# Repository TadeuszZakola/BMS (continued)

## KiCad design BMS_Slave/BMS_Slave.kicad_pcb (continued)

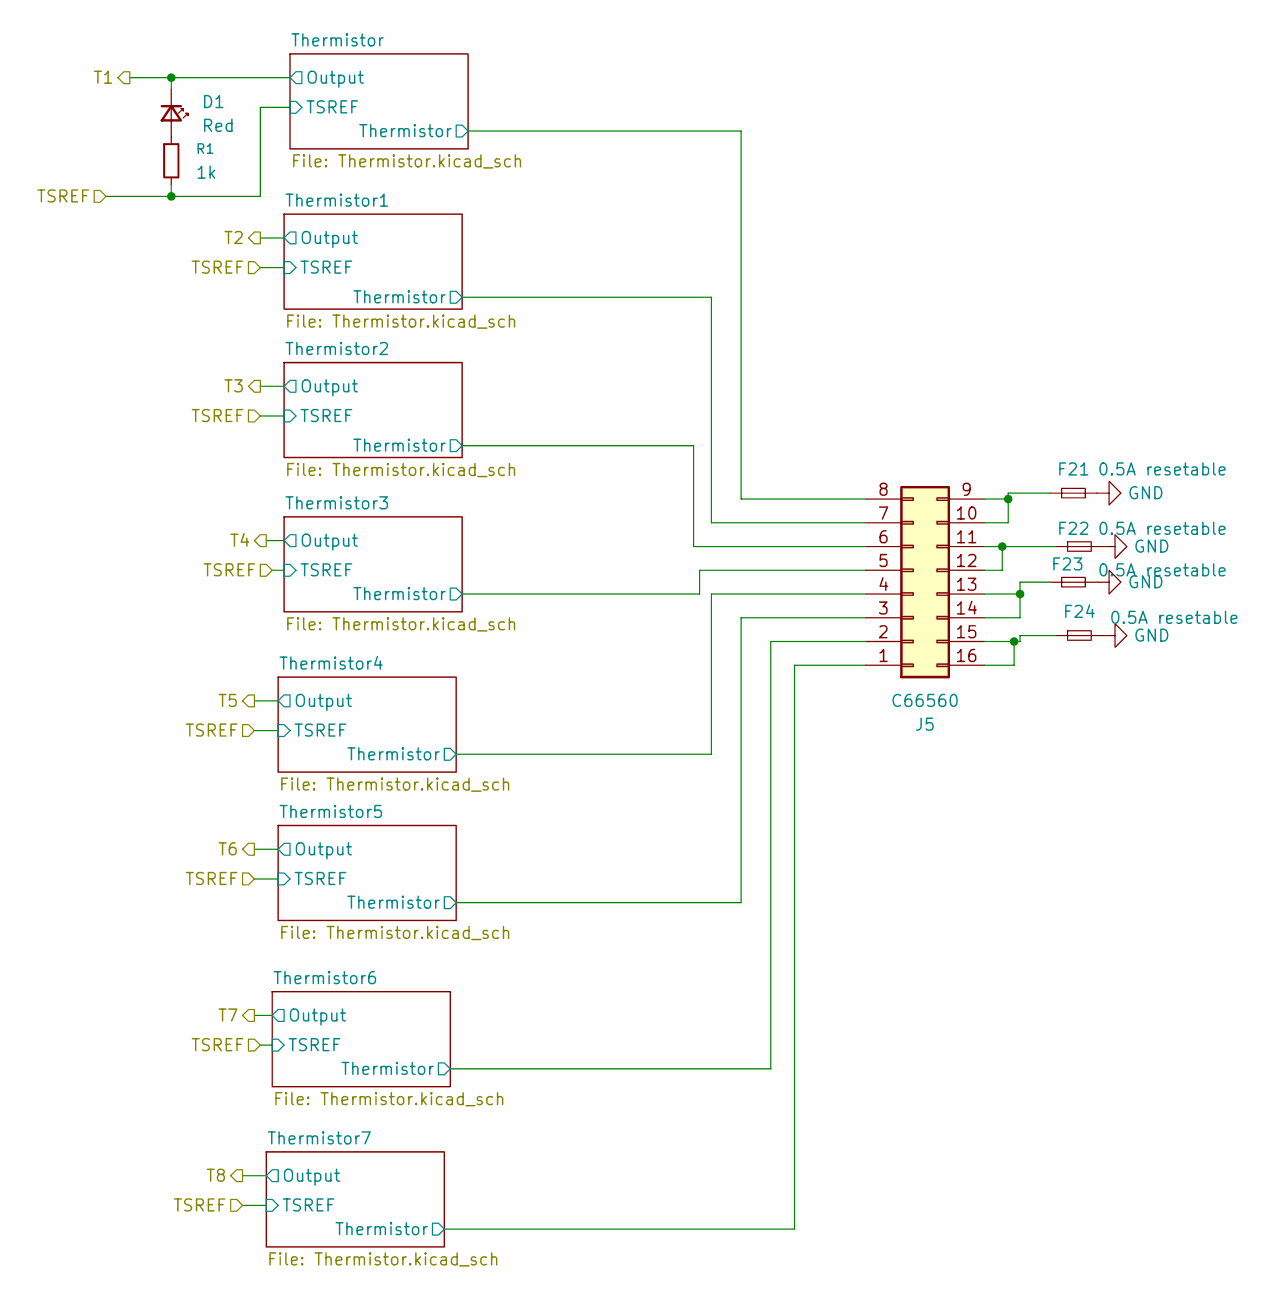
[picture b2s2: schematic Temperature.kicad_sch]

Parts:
D1: Red; LED_0603_1608Metric
F21, F22, F23, F24: 0.5A resetable; Fuse_0805_2012Metric
J5: C66560; JST_PHD_S16B-PHDSS_2x08_P2.00mm_Horizontal
R1: 1k; R_0603_1608Metric

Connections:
/Temperature/T1: D1.1 (K); also elsewhere on the board
/Temperature/TSREF: R1.2; also elsewhere on the board
/Temperature/Thermistor1/Thermistor: J5.7; also elsewhere on the board
/Temperature/Thermistor2/Thermistor: J5.6; also elsewhere on the board
/Temperature/Thermistor3/Thermistor: J5.5; also elsewhere on the board
/Temperature/Thermistor4/Thermistor: J5.4; also elsewhere on the board
/Temperature/Thermistor5/Thermistor: J5.3; also elsewhere on the board
/Temperature/Thermistor6/Thermistor: J5.2; also elsewhere on the board
/Temperature/Thermistor7/Thermistor: J5.1; also elsewhere on the board
/Temperature/Thermistor/Thermistor: J5.8; also elsewhere on the board
GND: F21.2, F22.2, F23.2, F24.2; also elsewhere on the board
unnamed: D1.2 (A), R1.1
unnamed: F21.1, J5.9, J5.10
unnamed: F22.1, J5.11, J5.12
unnamed: F23.1, J5.13, J5.14
unnamed: F24.1, J5.15, J5.16

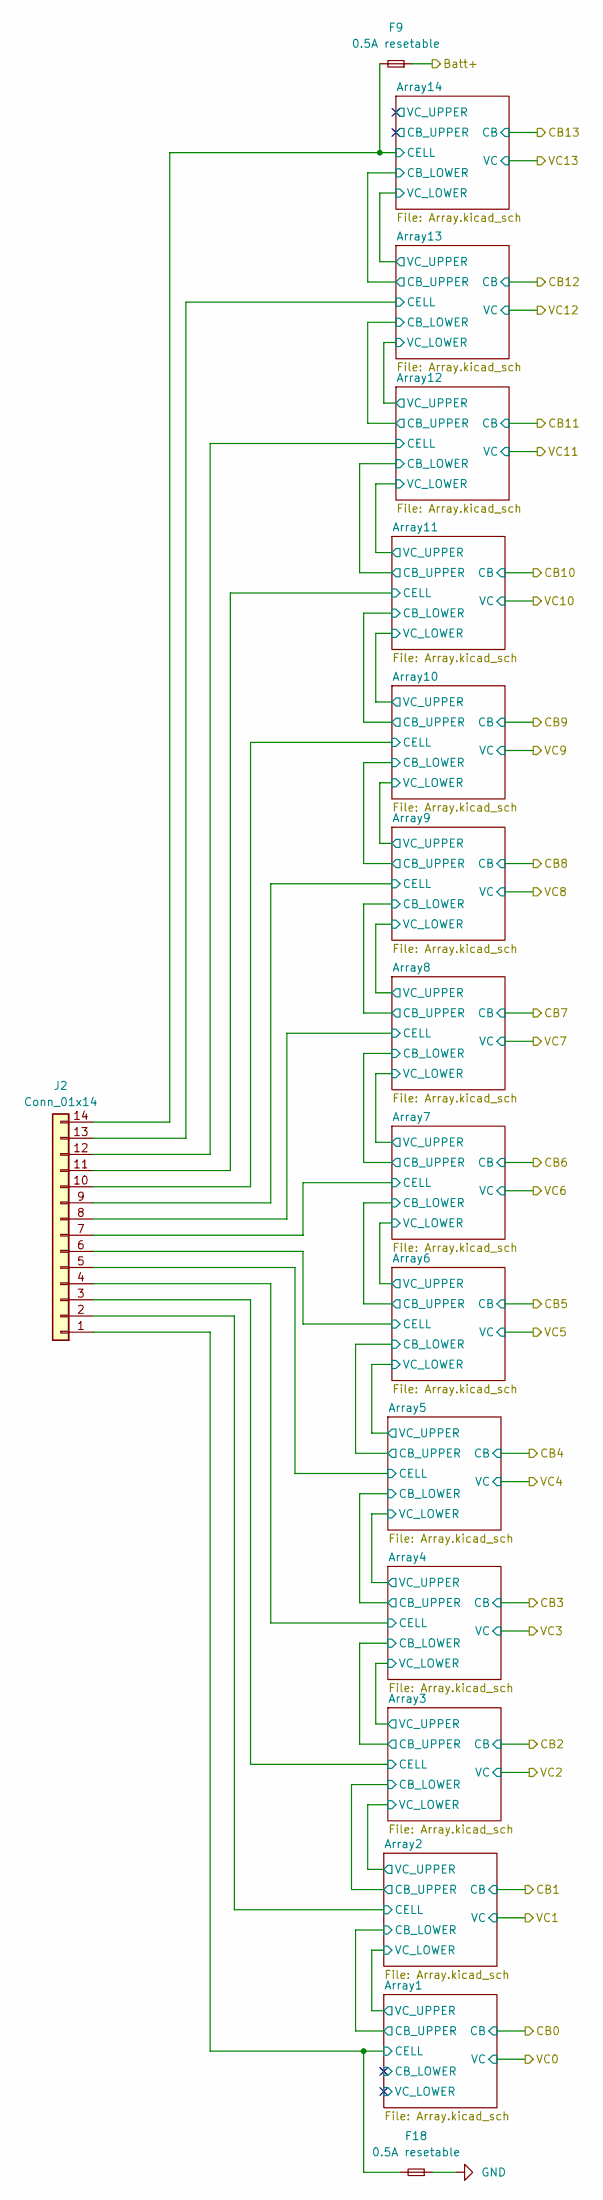
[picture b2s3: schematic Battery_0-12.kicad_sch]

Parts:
F9, F18: 0.5A resetable; Fuse_0805_2012Metric
J2: Conn_01x14; XY-XHB2.54-14A21

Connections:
/Battery/Array1/CELL: F18.2, J2.1; also elsewhere on the board
/Battery/Array2/CELL: J2.2; also elsewhere on the board
/Battery/Array3/CELL: J2.3; also elsewhere on the board
/Battery/Array4/CELL: J2.4; also elsewhere on the board
/Battery/Array5/CELL: J2.5; also elsewhere on the board
/Battery/Array6/CELL: J2.6; also elsewhere on the board
/Battery/Array7/CELL: J2.7; also elsewhere on the board
/Battery/Array8/CELL: J2.8; also elsewhere on the board
/Battery/Array9/CELL: J2.9; also elsewhere on the board
/Battery/Array10/CELL: J2.10; also elsewhere on the board
/Battery/Array11/CELL: J2.11; also elsewhere on the board
/Battery/Array12/CELL: J2.12; also elsewhere on the board
/Battery/Array13/CELL: J2.13; also elsewhere on the board
/Battery/Array14/CELL: F9.2, J2.14; also elsewhere on the board
/Battery/Batt+: F9.1; also elsewhere on the board
GND: F18.1; also elsewhere on the board

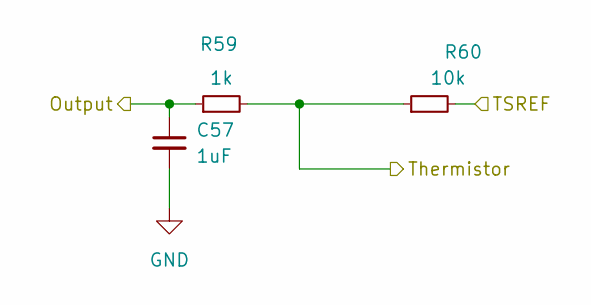
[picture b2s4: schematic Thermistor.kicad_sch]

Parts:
C57: 1uF; C_0603_1608Metric_Pad1.08x0.95mm_HandSolder
R59: 1k; R_0603_1608Metric_Pad0.98x0.95mm_HandSolder
R60: 10k; R_0603_1608Metric_Pad0.98x0.95mm_HandSolder

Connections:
/Temperature/T1: C57.1, R59.1; also elsewhere on the board
/Temperature/TSREF: R60.2; also elsewhere on the board
/Temperature/Thermistor/Thermistor: R59.2, R60.1; also elsewhere on the board
GND: C57.2; also elsewhere on the board

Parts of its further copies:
C58, C59, C60, C61, C62, C63, C64: 1uF; C_0603_1608Metric_Pad1.08x0.95mm_HandSolder
R61, R63, R65, R67, R69, R71, R73: 1k; R_0603_1608Metric_Pad0.98x0.95mm_HandSolder
R62, R64, R66, R68, R70, R72, R74: 10k; R_0603_1608Metric_Pad0.98x0.95mm_HandSolder

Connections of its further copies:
/Temperature/T2: C58.1, R61.1; also elsewhere on the board
/Temperature/T3: C59.1, R63.1; also elsewhere on the board
/Temperature/T4: C60.1, R65.1; also elsewhere on the board
/Temperature/T5: C61.1, R67.1; also elsewhere on the board
/Temperature/T6: C62.1, R69.1; also elsewhere on the board
/Temperature/T7: C63.1, R71.1; also elsewhere on the board
/Temperature/T8: C64.1, R73.1; also elsewhere on the board
/Temperature/TSREF: R62.2, R64.2, R66.2, R68.2, R70.2, R72.2, R74.2; also elsewhere on the board
/Temperature/Thermistor1/Thermistor: R61.2, R62.1; also elsewhere on the board
/Temperature/Thermistor2/Thermistor: R63.2, R64.1; also elsewhere on the board
/Temperature/Thermistor3/Thermistor: R65.2, R66.1; also elsewhere on the board
/Temperature/Thermistor4/Thermistor: R67.2, R68.1; also elsewhere on the board
/Temperature/Thermistor5/Thermistor: R69.2, R70.1; also elsewhere on the board
/Temperature/Thermistor6/Thermistor: R71.2, R72.1; also elsewhere on the board
/Temperature/Thermistor7/Thermistor: R73.2, R74.1; also elsewhere on the board
GND: C58.2, C59.2, C60.2, C61.2, C62.2, C63.2, C64.2; also elsewhere on the board

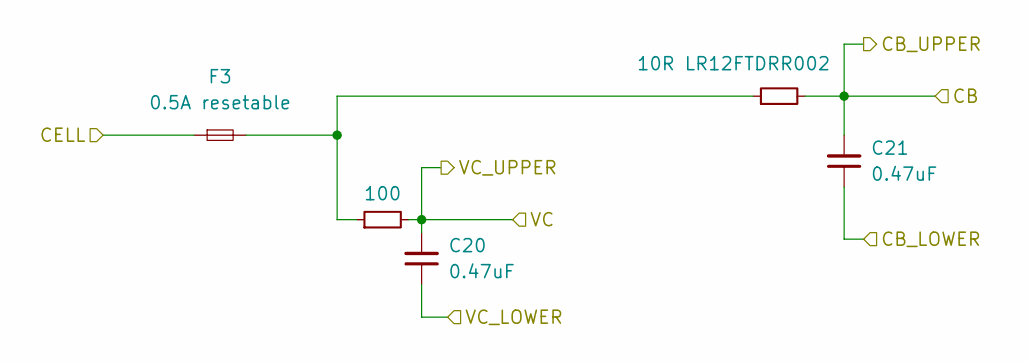
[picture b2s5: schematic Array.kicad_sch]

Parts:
C20, C21: 0.47uF; C_0603_1608Metric
F3: 0.5A resetable; Fuse_0805_2012Metric
R22: 100; R_0603_1608Metric
R35: 10R LR12FTDRR002; R_2512_6332Metric

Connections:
/Battery/Array1/CB_LOWER: C21.1
/Battery/Array1/CELL: F3.1; also elsewhere on the board
/Battery/Array1/VC_LOWER: C20.1
/CB0: C21.2, R35.2; also elsewhere on the board
/VC0: C20.2, R22.2; also elsewhere on the board
unnamed: F3.2, R22.1, R35.1

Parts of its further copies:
C22, C23, C24, C25, C26, C27, C28, C29, C30, C31, C32, C33, C34, C35, C36, C37, C38, C39, C40, C41, C42, C43, C44, C45, C46, C47: 0.47uF; C_0603_1608Metric
F4, F5, F6, F7, F8, F10, F11, F12, F13, F14, F15, F16, F17: 0.5A resetable; Fuse_0805_2012Metric
R23, R24, R25, R26, R27, R28, R29, R30, R31, R32, R33, R34, R48: 100; R_0603_1608Metric
R36, R37, R38, R39, R40, R41, R42, R43, R44, R45, R46, R47, R49: 10R LR12FTDRR002; R_2512_6332Metric

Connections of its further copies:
/Battery/Array2/CELL: F4.1; also elsewhere on the board
/Battery/Array3/CELL: F5.1; also elsewhere on the board
/Battery/Array4/CELL: F6.1; also elsewhere on the board
/Battery/Array5/CELL: F7.1; also elsewhere on the board
/Battery/Array6/CELL: F8.1; also elsewhere on the board
/Battery/Array7/CELL: F10.1; also elsewhere on the board
/Battery/Array8/CELL: F11.1; also elsewhere on the board
/Battery/Array9/CELL: F12.1; also elsewhere on the board
/Battery/Array10/CELL: F13.1; also elsewhere on the board
/Battery/Array11/CELL: F14.1; also elsewhere on the board
/Battery/Array12/CELL: F15.1; also elsewhere on the board
/Battery/Array13/CELL: F16.1; also elsewhere on the board
/Battery/Array14/CELL: F17.1; also elsewhere on the board
/CB0: C23.1; also elsewhere on the board
/CB1: C23.2, C25.1, R36.2; also elsewhere on the board
/CB2: C25.2, C27.1, R37.2; also elsewhere on the board
/CB3: C27.2, C29.1, R38.2; also elsewhere on the board
/CB4: C29.2, C31.1, R39.2; also elsewhere on the board
/CB5: C31.2, C33.1, R40.2; also elsewhere on the board
/CB6: C33.2, C35.1, R41.2; also elsewhere on the board
/CB7: C35.2, C37.1, R42.2; also elsewhere on the board
/CB8: C37.2, C39.1, R43.2; also elsewhere on the board
/CB9: C39.2, C41.1, R44.2; also elsewhere on the board
/CB10: C41.2, C43.1, R45.2; also elsewhere on the board
/CB11: C43.2, C45.1, R46.2; also elsewhere on the board
/CB12: C45.2, C47.1, R47.2; also elsewhere on the board
/CB13: C47.2, R49.2; also elsewhere on the board
/VC0: C22.1; also elsewhere on the board
/VC1: C22.2, C24.1, R23.2; also elsewhere on the board
/VC2: C24.2, C26.1, R24.2; also elsewhere on the board
/VC3: C26.2, C28.1, R25.2; also elsewhere on the board
/VC4: C28.2, C30.1, R26.2; also elsewhere on the board
/VC5: C30.2, C32.1, R27.2; also elsewhere on the board
/VC6: C32.2, C34.1, R28.2; also elsewhere on the board
/VC7: C34.2, C36.1, R29.2; also elsewhere on the board
/VC8: C36.2, C38.1, R30.2; also elsewhere on the board
/VC9: C38.2, C40.1, R31.2; also elsewhere on the board
/VC10: C40.2, C42.1, R32.2; also elsewhere on the board
/VC11: C42.2, C44.1, R33.2; also elsewhere on the board
/VC12: C44.2, C46.1, R34.2; also elsewhere on the board
/VC13: C46.2, R48.2; also elsewhere on the board
unnamed: F4.2, R23.1, R36.1
unnamed: F5.2, R24.1, R37.1
unnamed: F6.2, R25.1, R38.1
unnamed: F7.2, R26.1, R39.1
unnamed: F8.2, R27.1, R40.1
unnamed: F10.2, R28.1, R41.1
unnamed: F11.2, R29.1, R42.1
unnamed: F12.2, R30.1, R43.1
unnamed: F13.2, R31.1, R44.1
unnamed: F14.2, R32.1, R45.1
unnamed: F15.2, R33.1, R46.1
unnamed: F16.2, R34.1, R47.1
unnamed: F17.2, R48.1, R49.1

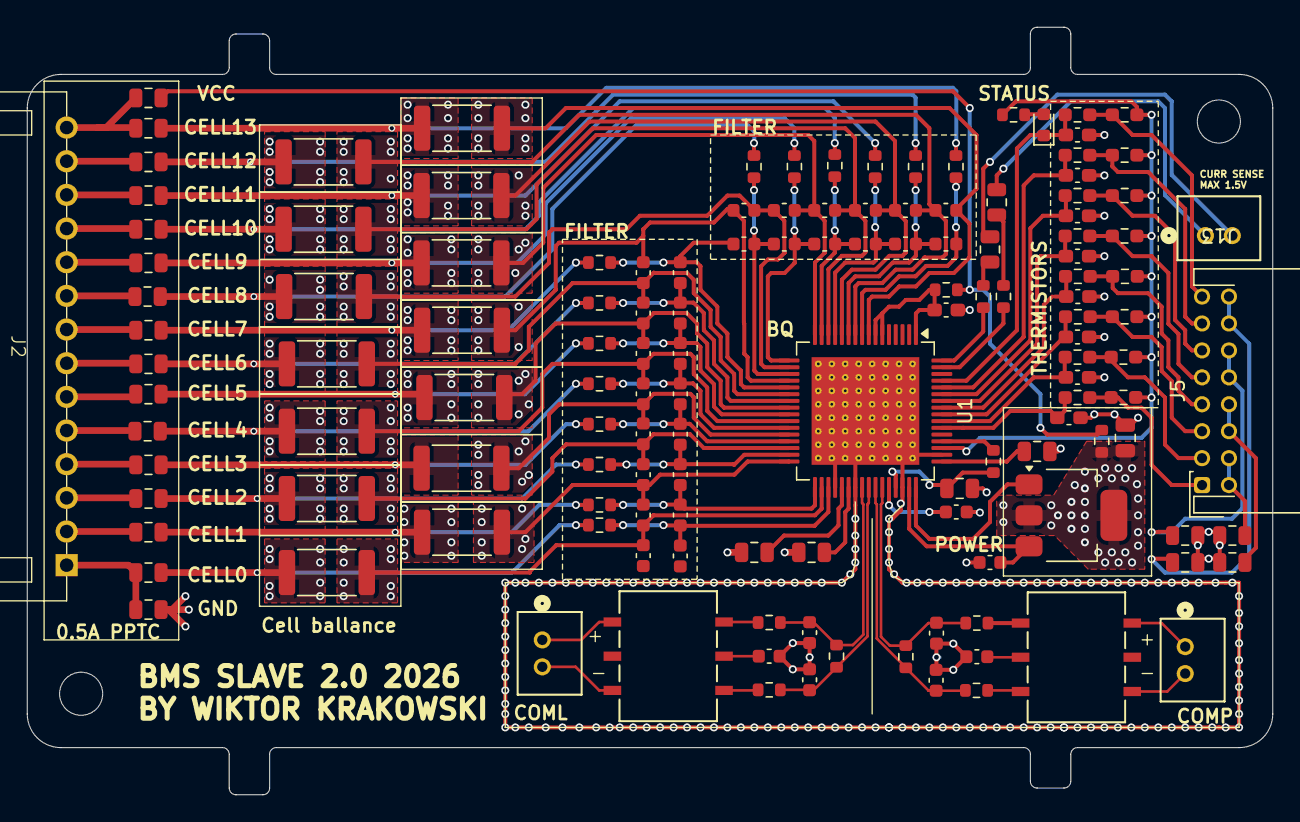
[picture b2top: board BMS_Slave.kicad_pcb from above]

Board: 4 copper layers, 92.5 x 57.0 mm, 140 parts (0 on the bottom side), 110 nets.

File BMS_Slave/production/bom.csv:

Designator,Footprint,Quantity,Value,LCSC Part #
C2,0805,1,0.22uF,
"C20, C21, C22, C23, C24, C25, C26, C27, C28, C29, C30, C31, C32, C33, C34, C35, C36, C37, C38, C39, C40, C41, C42, C43, C44, C45, C46, C47",0603,28,0.47uF,
"C3, C9",0603,2,0.1uF,
C4,0603,1,10nF,
"C48, C49, C50, C51, C52, C53",0603,6,220pF,
"C5, C8",0805,2,1uF,
"C57, C58, C59, C60, C61, C62, C63, C64",0603,8,1uF,
C6,0805,1,4.7uF,
C7,0805,1,2.2uF,
"F10, F11, F12, F13, F14, F15, F16, F17, F18, F3, F4, F5, F6, F7, F8, F9",0805,16,0.5A resetable,
"J1, J16, J17, J18, J19, J20, J21, J22, J23, J24, J25, J26, J27, J28, J29, J30",SolderWirePad_1x01_SMD_2x4mm,16,Conn_01x01_Socket,
J10,SolderWirePad_1x01_SMD_5x10mm,1,Batt 7,
J11,SolderWirePad_1x01_SMD_5x10mm,1,Batt 6,
J12,SolderWirePad_1x01_SMD_5x10mm,1,Batt 2,
J13,SolderWirePad_1x01_SMD_5x10mm,1,Batt 5,
J14,SolderWirePad_1x01_SMD_5x10mm,1,Batt 1,
J15,SolderWirePad_1x01_SMD_5x10mm,1,Batt 0,
J2,SolderWirePad_1x01_SMD_5x10mm,1,Batt 13,
J3,SolderWirePad_1x01_SMD_5x10mm,1,Batt 12,
"J33, J34",DSUB-9_Pins_Vertical_P2.77x2.84mm_MountingHoles,2,Dsub 9,
J4,SolderWirePad_1x01_SMD_5x10mm,1,Batt 11,
J5,SolderWirePad_1x01_SMD_5x10mm,1,Batt 10,
J6,SolderWirePad_1x01_SMD_5x10mm,1,Batt 9,
J7,SolderWirePad_1x01_SMD_5x10mm,1,Batt 8,
J8,SolderWirePad_1x01_SMD_5x10mm,1,Batt 4,
J9,SolderWirePad_1x01_SMD_5x10mm,1,Batt 3,
Q8,SOT-223-3_TabPin2,1,FZT653TA,
R2,0603,1,300,
"R22, R23, R24, R25, R26, R27, R28, R29, R30, R31, R32, R33, R34, R48",0603,14,100,
"R35, R36, R37, R38, R39, R40, R41, R42, R43, R44, R45, R46, R47, R49",2512,14,10R LR12FTDRR002,
R4,0603,1,30,
R5,0603,1,0R,
"R58, R59, R61, R63, R65, R67, R69, R71, R73, R77",0603,10,1k,
"R60, R62, R64, R66, R68, R70, R72, R74",0603,8,10k,
"R75, R76, R78, R79",0603,4,49,
"T2, T3",IC6_SM91502ALA-E_BRN,2,TM0608SR,
U1,Texas_TQFP-64-1EP_10x10mm_P0.5mm_EP8x8mm_Mask4.44x4.44mm_ThermalVias,1,BQ79614PAPRQ1,

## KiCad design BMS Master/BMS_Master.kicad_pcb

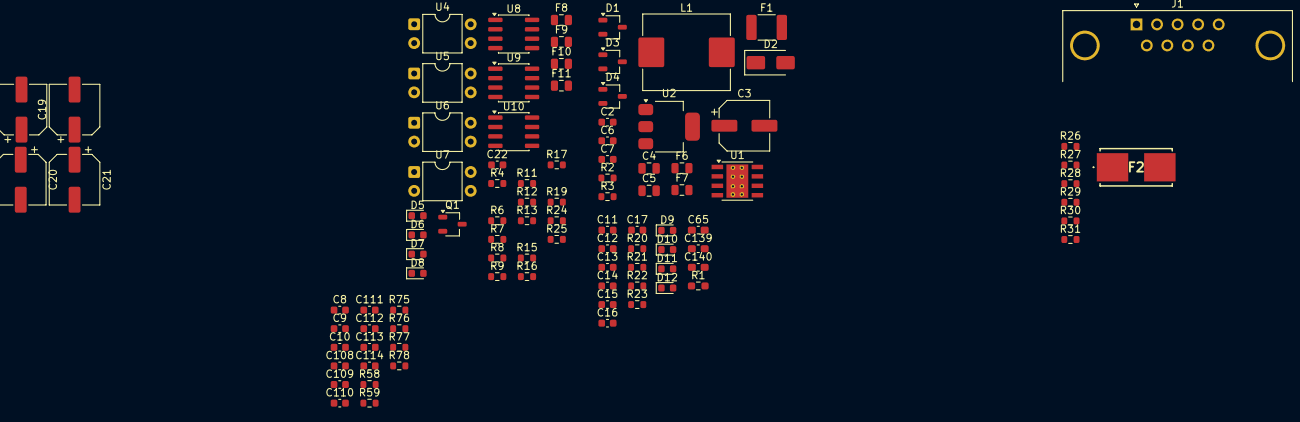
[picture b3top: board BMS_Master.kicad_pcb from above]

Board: 2 copper layers, 96 parts (0 on the bottom side), 48 nets, no tracks yet.

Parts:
C2, C6, C7, C8, C9, C10, C11, C12, C13, C14, C15, C16, C17, C22: CC0603KRX7R9BB104; C_0603_1608Metric
C3, C18, C19, C20, C21: MS221M160E5R8R4Z00ZZ; CP_Elec_6.3x5.8
C4, C5: CL21B224KBFNNNE; C_0805_2012Metric
C65: 1uF; C_0603_1608Metric_Pad1.08x0.95mm_HandSolder
C108, C109, C110, C111, C112, C113, C114: CL10B224KA8NNNC; C_0603_1608Metric
C139, C140: 2.2n; C_0603_1608Metric_Pad1.08x0.95mm_HandSolder
D1, D3, D4: PSM712-LF-T7; TSOT-23
D2: B340A; D_SMA
D5, D6, D7, D8, D9, D10, D11, D12: KT-0603R; LED_0603_1608Metric
F1: SMD1812P200TF16; C_1812_4532Metric
F2: 01550900M
F6, F7, F8, F9, F10, F11: 0.5A resetable; Fuse_0805_2012Metric
J1: DE9_Pins; DSUB-9_Pins_Horizontal_P2.77x2.84mm_EdgePinOffset4.94mm_Hou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
L1: CYA1040-15UH; L_Chilisin_BMRF00101040
Q1: AO3401A; TSOT-23
R1: 100k; R_0603_1608Metric_Pad0.98x0.95mm_HandSolder
R2: 0603WAF1002T5E; R_0603_1608Metric
R3: 0603WAF3301T5E; R_0603_1608Metric
R4, R11, R15, R19: 0603WAF2200T5E; R_0603_1608Metric
R6, R7, R13, R17: 0603WAF4991T5E; R_0603_1608Metric
R8, R9, R12, R16, R20, R21, R22, R23, R25, R30, R31: 0603WAF1000T5E; R_0603_1608Metric
R24, R26, R27, R28, R29, R58: 0603WAF1001T5E; R_0603_1608Metric
R59: 1k; R_0603_1608Metric
R75, R76, R77, R78: 0603WAF499JT5E; R_0603_1608Metric
U1: TPS5430DDA; TI_SO-PowerPAD-8_ThermalVias
U2: AMS1117-3.3; SOT-223-3_TabPin2
U4, U5, U6, U7: LTV-817; DIP-4_W7.62mm
U8: ACS711ELCTR-12AB-T; SOIC-8_3.9x4.9mm_P1.27mm
U9, U10: ACS711xLCTR-12AB; SOIC-8_3.9x4.9mm_P1.27mm

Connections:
/BQ Interface/5V: C10.1, C108.1
/BQ Interface/COMHN: C111.1, R58.1, R76.1
/BQ Interface/COMHP: C110.1, R58.2, R75.1
/BQ Interface/COMLN: C113.1, R59.1, R78.1
/BQ Interface/COMLP: C112.1, R59.2, R77.1
/Power/3.3V: C6.1, C7.1, D4.1 (A1), D4.2 (A2), F7.2
/Power/5V: C5.1, D3.1 (A1), D3.2 (A2), F1.2, U2.3 (VI)
/STM/3.3V: C11.1, C12.2, C13.2, C14.1, C15.1, C16.1, C17.1, C65.2, R20.1, R21.1, R22.1, R23.1
/STM_IO/3.3V: C22.1, R6.1, R7.1, R13.1, R17.1, R26.2, R27.2, R28.2, R29.2, U8.8 (VCC)
/STM_IO/Power_output_1: J1.5 (5_5), U8.3 (IP-), U8.4 (IP-)
GND: C3.2, C4.2, C5.2, C6.2, C7.2, C8.2, C9.1, C10.2, C11.2, C12.1, C13.1, C14.2, C15.2, C16.2, C17.2, C65.1, C108.2, C109.2, C110.2, C111.2, C112.2, C113.2, C114.2, C139.1, D1.3 (common), D2.2 (A), D3.3 (common), D4.3 (common), R1.1, R3.2, U1.6 (GND), U1.9 (GNDPAD), U2.1 (GND)
unnamed: C3.1, F1.1, L1.2, R2.1
unnamed: C18.2, C19.2, C20.2, C21.2
unnamed: D1.1 (A1), D1.2 (A2), F6.2, U1.7 (VIN)
unnamed: C2.2, D2.1 (K), L1.1, U1.8 (PH)
unnamed: D5.2 (A), R29.1
unnamed: D5.1 (K), R6.2, R8.2, U4.4
unnamed: D6.2 (A), R7.2, R9.2, U5.4
unnamed: D6.1 (K), R28.1
unnamed: D7.2 (A), R12.2, R13.2, U6.4
unnamed: D7.1 (K), R27.1
unnamed: D8.2 (A), R16.2, R17.2, U7.4
unnamed: D8.1 (K), R26.1
unnamed: D9.2 (A), R20.2
unnamed: D10.2 (A), R21.2
unnamed: D11.2 (A), R22.2
unnamed: D12.2 (A), R23.2
unnamed: F2.2, U8.1 (IP+), U8.2 (IP+)
unnamed: F8.1, R4.1
unnamed: F9.1, R11.1
unnamed: F10.1, R15.1
unnamed: F11.1, R19.1
unnamed: C18.1, C19.1, C20.1, C21.1, Q1.3 (D), R24.1
unnamed: Q1.1 (G), R24.2, R25.2
unnamed: F2.1, Q1.2 (S)
unnamed: R4.2, U4.1
unnamed: R11.2, U5.1
unnamed: R15.2, U6.1
unnamed: R19.2, U7.1
unnamed: C2.1, U1.1 (BOOT)
unnamed: R2.2, R3.1, U1.4 (VSENSE)
unnamed: C4.1, F7.1, U2.2 (VO)
unnamed: R30.2, U8.7 (VIOUT)
unnamed: R31.2, U8.6 (~FAULT)
unnamed: U9.1 (IP+), U9.2 (IP+)
unnamed: U9.3 (IP-), U9.4 (IP-)
unnamed: U10.1 (IP+), U10.2 (IP+)
unnamed: U10.3 (IP-), U10.4 (IP-)

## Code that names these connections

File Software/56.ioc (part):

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Mcu.Name=STM32H742V(G-I)Tx
Mcu.Package=LQFP100
Mcu.UserName=STM32H742VITx
PA0.Mode=Asynchronous
PA0.Signal=UART4_TX
PA1.Mode=Asynchronous
PA1.Signal=UART4_RX
PA11.Mode=Device_Only
PA11.Signal=USB_OTG_FS_DM
PA12.Mode=Device_Only
PA12.Signal=USB_OTG_FS_DP
PA13\ (JTMS/SWDIO).Mode=Serial_Wire
PA13\ (JTMS/SWDIO).Signal=DEBUG_JTMS-SWDIO
PA14\ (JTCK/SWCLK).Mode=Serial_Wire
PA14\ (JTCK/SWCLK).Signal=DEBUG_JTCK-SWCLK
PA2.Signal=GPIO_Input
PA5.Signal=GPIO_Output
PA6.Signal=GPIO_Output
PB1.Signal=ADCx_INP5
PB10.Signal=GPIO_Input
PB11.Signal=GPIO_Input
PC4.Signal=ADCx_INP4
PC7.Signal=GPIO_Output
PC8.Signal=GPIO_Output
PE14.Signal=GPIO_Input
PE15.Signal=GPIO_Input
PE2.Signal=GPIO_Output
PE3.Signal=GPIO_Output
PE4.Signal=GPIO_Output
PE5.Signal=GPIO_Output
RCC.SYSCLKFreq_VALUE=64000000
board=custom

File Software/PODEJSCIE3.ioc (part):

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Mcu.Name=STM32H742V(G-I)Tx
Mcu.Package=LQFP100
Mcu.UserName=STM32H742VITx
PA0.Mode=Asynchronous
PA0.Signal=UART4_TX
PA1.Mode=Asynchronous
PA1.Signal=UART4_RX
PA11.Mode=Device_Only
PA11.Signal=USB_OTG_FS_DM
PA12.Mode=Device_Only
PA12.Signal=USB_OTG_FS_DP
PA13\ (JTMS/SWDIO).Mode=Serial_Wire
PA13\ (JTMS/SWDIO).Signal=DEBUG_JTMS-SWDIO
PA14\ (JTCK/SWCLK).Mode=Serial_Wire
PA14\ (JTCK/SWCLK).Signal=DEBUG_JTCK-SWCLK
PA5.Signal=GPIO_Output
PB10.Signal=GPIO_Input
PB11.Signal=GPIO_Input
PB14.Mode=Device_Only_FS
PB14.Signal=USB_OTG_HS_DM
PB15.Mode=Device_Only_FS
PB15.Signal=USB_OTG_HS_DP
PC4.Signal=ADCx_INP4
PC7.Signal=GPIO_Output
PC8.Signal=GPIO_Output
PD0.Mode=FDCAN_Activate
PD0.Signal=FDCAN1_RX
PD1.Mode=FDCAN_Activate
PD1.Signal=FDCAN1_TX
PE14.Signal=GPIO_Input
PE15.Signal=GPIO_Input
PE2.Signal=GPIO_Output
PE3.Signal=GPIO_Output
PE4.Signal=GPIO_Output
PE5.Signal=GPIO_Output
RCC.SYSCLKFreq_VALUE=76000000
RCC.SYSCLKSource=RCC_SYSCLKSOURCE_PLLCLK
board=custom

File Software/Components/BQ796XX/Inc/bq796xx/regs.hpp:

#pragma once

#include "main.h"

#include "utils.hpp"

namespace PUTM
{
    namespace Bq796xx
    {
        namespace Types
        {   
            enum struct ScanMode : uint8_t
            {
                Stop,
                RoundRobin,
                Once,
                SingleChannel
            };

            enum struct GpioMode : uint8_t
            {
                HighZ,
                AdcOtut
            };
        }

        namespace Regs
        {
            struct __packed Control1 : public Utils::IReg<0x0309>
            {
                bool addr_wr : 1 { 0b0 };
                bool soft_reset : 1 { 0b0 };
                bool goto_sleep : 1 { 0b0 };
                bool goto_shutdown : 1 { 0b0 };
                bool send_slptoact : 1 { 0b0 };
                bool send_wake : 1 { 0b0 };
                bool send_shutdown : 1 { 0b0 };
                bool dir_sel : 1 { 0b0 };
            };

            struct __packed AdcCtrl1 : public Utils::IReg<0x030d>
            {
                Types::ScanMode main_mode : 2 { Types::ScanMode::Stop };
                bool main_go : 1 { 0b0 };
                bool lpf_cell_en : 1 { 0b0 };
                bool lpf_bb_en : 1 { 0b0 };
                uint8_t reserved : 3 { 0b000 };
            };
    
            struct __packed OVUVCtrl : public Utils::IReg<0x032C>
            {
                Types::ScanMode ovuv_mode : 2 { Types::ScanMode::Stop };
                bool ovuv_go : 1 { false };
                uint8_t ovuv_lock : 4 { 0 };
                uint8_t vcbdone_thr_lock : 1 { 0 };
            };

            struct __packed GPIOConf1 : public Utils::IReg<0x000E>
            {
                Types::GpioMode gpio1 : 3 { Types::GpioMode::HighZ };
                Types::GpioMode gpio2 : 3 { Types::GpioMode::HighZ };
                bool spi_en : 1 { false };
                bool fault_in_en : 1 { false };
            };

            struct __packed GPIOConf2 : public Utils::IReg<0x000F>
            {
                Types::GpioMode gpio3 : 3 { Types::GpioMode::HighZ };
                Types::GpioMode gpio4 : 3 { Types::GpioMode::HighZ };
                bool reserved : 1 { false };
                bool spare : 1 { false };
            };

            struct __packed GPIOConf3 : public Utils::IReg<0x0010>
            {
                Types::GpioMode gpio5 : 3 { Types::GpioMode::HighZ };
                Types::GpioMode gpio6 : 3 { Types::GpioMode::HighZ };
                uint8_t spare : 2 { 0x00 };
            };

            struct __packed GPIOConf4 : public Utils::IReg<0x0011>
            {
                Types::GpioMode gpio7 : 3 { Types::GpioMode::HighZ };
                Types::GpioMode gpio8 : 3 { Types::GpioMode::HighZ };
                uint8_t spare : 2 { 0x00 };
            };

            struct __packed OTUTThresh : public Utils::IReg<0x000B>
            {
                uint8_t ot_thr : 5 { 0x00 };
                uint8_t ut_thr : 3 { 0x00 };
            };

            struct __packed OTUTCtrl : public Utils::IReg<0x032D>
            {
                Types::ScanMode otut_mode : 2 { Types::ScanMode::Stop };
                bool otut_go : 1 { false };
                uint8_t otut_lock : 3 { 0 };
                uint8_t vcbdone_thr_lock : 1 { 0 };
                uint8_t reserved : 1 { 0 };
            };
        }
    }
}

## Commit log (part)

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2025-03-21 zmiany w bq79614 layout
2025-03-24 zmiana polozenia zlacza oraz ukladu bq, jak i zmiena via na thru
2025-04-01 Dodano layout drugiego bq79614, ukladu tlumaczącego z protokułu TI na UART oraz wstępnie poprowadzono pary różnicowe
2025-04-04 Iteracja 1.0 gotowa, teraz sprawdzenie i zmiany kosmetyczne
2025-04-06 poprawy
2025-04-08 Zmienione kondensatory na kondensatory bezpieczeństwa,poprawiono strefy na thermal relief oraz naprawiono bledy z tym zwiazane, impedancja do zmiany jeszcze
2025-04-10 Zmieniono złącza, zmieniono kondensatory na kondensatory bezpieczeństwa, poprawiono masę oraz dodano podział na hardware i software
2025-04-11 Dodano diody TVS na każdej części zasilania, zmieniono bezpieczniki, podzielono bezpieczniki na bezpieczniki do prądów wewnętrznych oraz zewnętrznych,poprawiono małe błedy
2025-04-12 Dodano wyjaśnienia w schemacie, zmieniono nazewnictwo wewnętrzne lini can
2025-04-13 dodano pozostale datasheety, zmieniono blad w usb
2025-04-13 to samo
2025-04-22 Zmiany wizualne na płytce, poprawiono ulozenie elementow na masce dekoracyjnej
2025-04-25 Wiecej zmian wizualnych pod produkcje
2025-04-27 poprawiono impedancje na lini usb na 89ohm ( w zakresie)
2025-04-27 poprawiono impedancje na sciezkach sygnalowych miedzy ukladami bq
2025-04-27 Wersja V1.0 gotowa, wysłana do produckji
2025-05-06 Male zmiany
2025-05-20 Fixed boot resistor ground
2025-07-15 zmiany w kodzier bq
2025-08-05 Po 2 miesiącach walki pierwszy działający kod do BMS'A, odczyt napięc działa, over/under voltage protection w trakcie testów
2025-08-08 Przeniesiono projekt na FreeRTOS, podzielono na taski oraz dodano pozostałe definicje (can, usb,przyciski itp)
2025-08-14 Dodano wysyłanie danych do komputera na usb za pomocą portu szeregowego, podstawy pod pomiary temperatur
2025-08-24 Pomiary temperatury nie sparwne, pomiar temperatur BQ79614 poprawny, krytyczne jest odpowiednie opoźnienie odczytów
2025-08-25 W pełni działające OV oraz UV obliczane w bq79614 a nie w stm32
2025-09-02 Dodano podstawy komunikacji CAN , nie przeprowadzono jescze weryfikacji działania kodu
2025-09-09 Dodano działające pomiary temperatury bazujące na regresji liniowej symulowanych pomiarów
2025-09-09 Dodano jedną funckje inicjalizacji, zaktualizowano z gitem
2025-10-13 Dodano komunikację dwukierunkową po porcie szeregowym, zaprojektowano , zaimplementowano automatyczne balansowanie, zaprojektowano aplikacje diagnostyczną w pythonie
2025-10-13 Wrzucenie poprawej wersji softu
2025-10-20 Rezygnacja z FREERTOS
2025-11-16 Poprawiono impedancje lini can
2025-11-22 Dodano logikę ładowania bateri, zabezpieczenia OV UV na przekaźniku działają poprawnie, przekaźnik ma swój test polegający na styku pomocniczym
2025-12-16 Zaktualizowano backupy oraz dodano pomiar prądu
2026-01-03 Zmiany wizualne w schemacie
